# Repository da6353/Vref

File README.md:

# Vref
Virtual ground, in a PDIP8 package

Based on this paper: https://www.ti.com/lit/an/sbva002/sbva002.pdf

https://l.facebook.com/l.php?u=https%3A%2F%2Fgithub.com%2Fda6353%2FVref%3Ffbclid%3DIwZXh0bgNhZW0CMTEAAR1YYSdaZmJQTInOCMU4OK5hUXoQJnnteBDRCC_r7G96EA1hHZP52402e3k_aem_pgm3NdlbhVuk-1I4EkfesA&h=AT10sP992uQ2v7GivCy05ZsJV2U-RpoUXTEONibHl7-vwVt3iGbaf28fRjfjl0zNPMJ7LhQa40hGEv78saXLO7Caq5pcPyhiaEnxdyNE4-u_cSICnrpTv1C4xrrQHkVa8MkdlvljCcTv&s=1

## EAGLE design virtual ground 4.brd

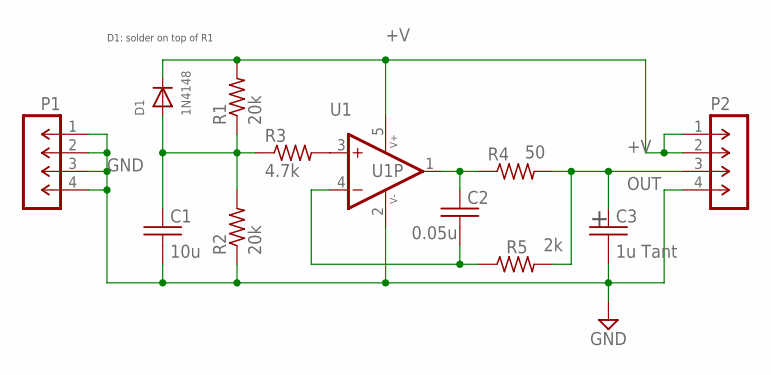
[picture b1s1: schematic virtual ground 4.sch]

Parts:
C1: 10u; C0805
C2: 0.05u; C0805
C3: 1u Tant; C0805
D1: 1N4148; SOD-323F
P1: M-1X04-SIP-100-40; SIP-100-04-40
P2: M-1X04-; SIP-100-04-40_DON
R1, R2: 20k; R0805
R3: 4.7k; R0805
R4: 50; R0805
R5: 2k; R0805
U1: TLV9301IDBVR; SOT23-5

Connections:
+V: D1.C, P2.1, P2.2, R1.2, U1.5 (V+)
GND: C1.2, C3.2, P1.1, P1.2, P1.3, P1.4, P2.4, R2.1, U1.2 (V-)
unnamed: R3.2, U1.3 (+IN)
unnamed: C2.2, R5.1, U1.4 (-IN)
unnamed: C1.1, D1.A, R1.1, R2.2, R3.1
unnamed: C2.1, R4.1, U1.1 (OUT)
OUT: C3.1, P2.3, R4.2, R5.2

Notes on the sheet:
D1: solder on top of R1

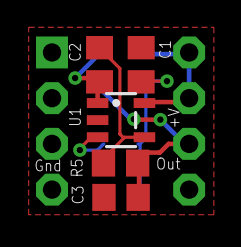
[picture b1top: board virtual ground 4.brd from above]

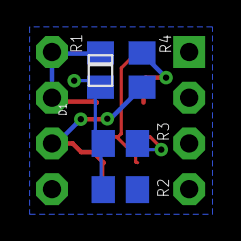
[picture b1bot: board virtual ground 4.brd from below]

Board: 2 copper layers, 12 parts (5 on the bottom side), 7 nets.

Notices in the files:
parts and their libraries:
con-headers-jp: Copyright (C) 2008, Bob Starr
op-amp: Copyright (C) 2015, Bob Starr
